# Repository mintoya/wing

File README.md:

# My wireless-ish split keyboard project

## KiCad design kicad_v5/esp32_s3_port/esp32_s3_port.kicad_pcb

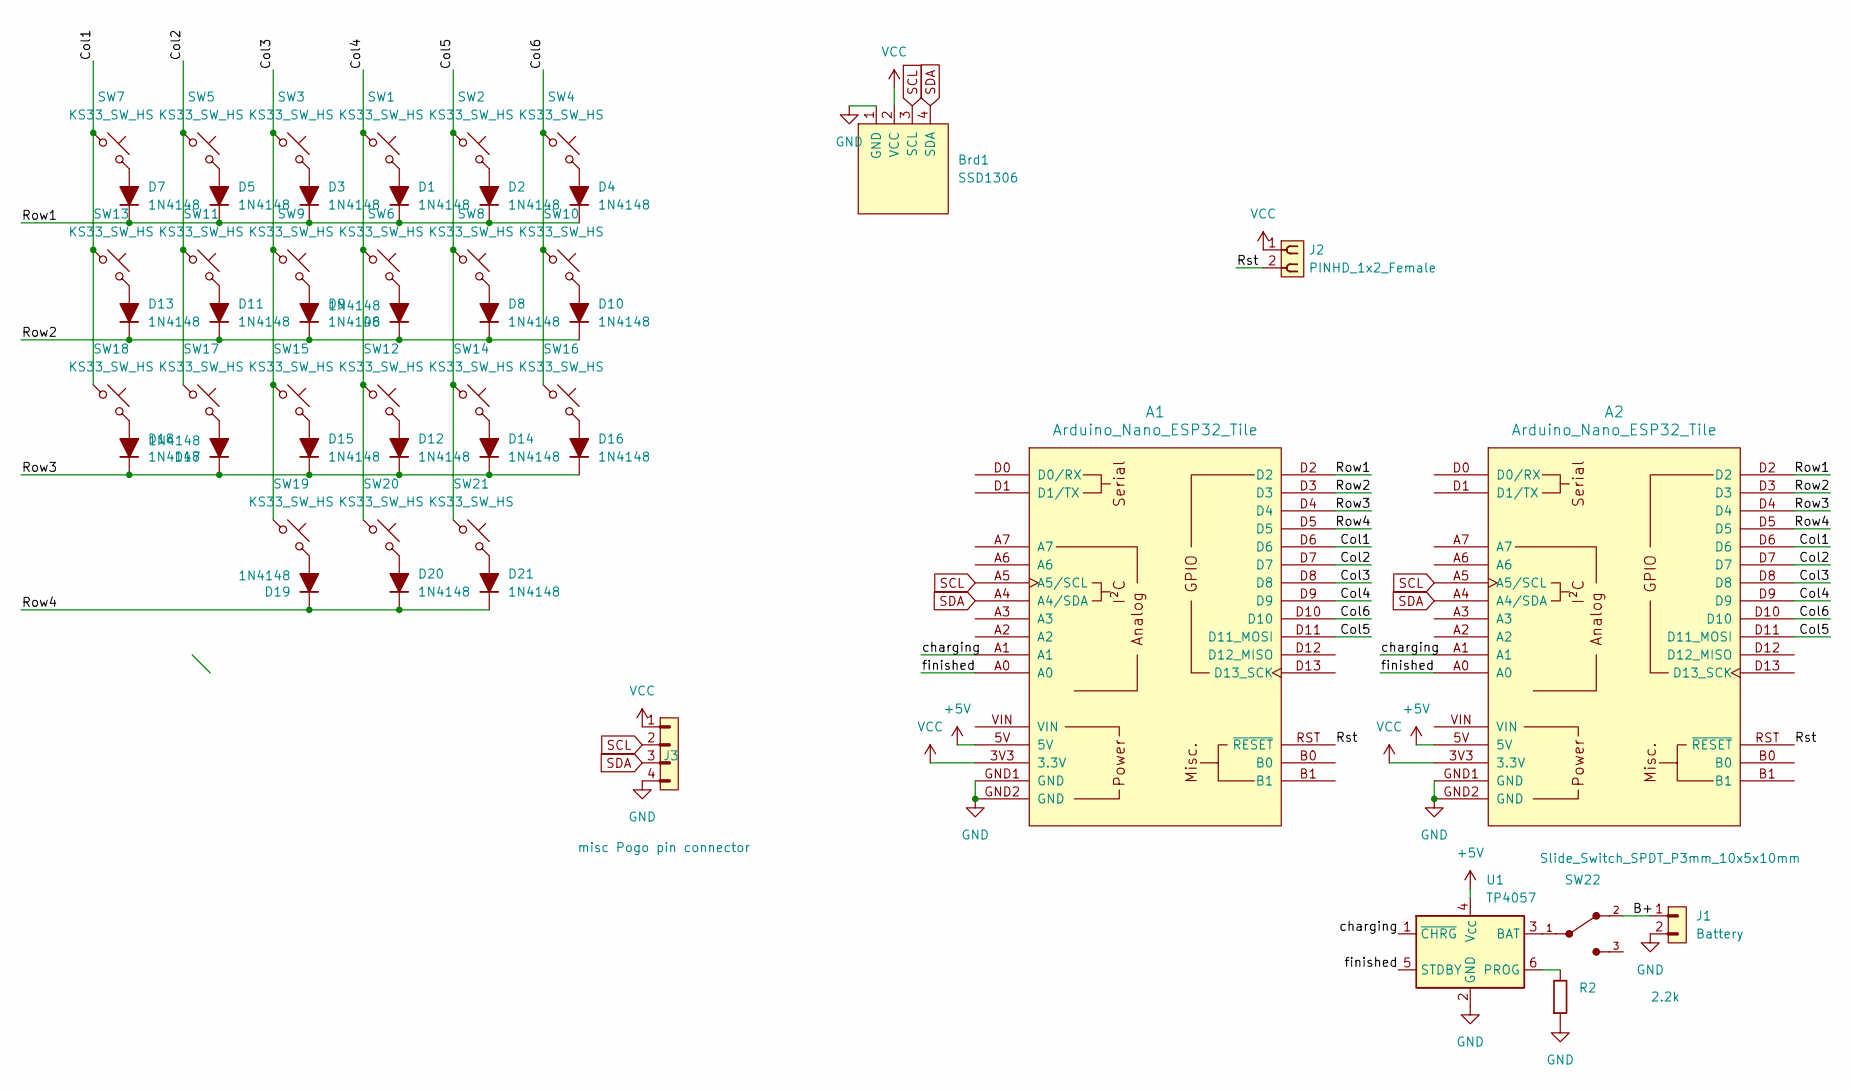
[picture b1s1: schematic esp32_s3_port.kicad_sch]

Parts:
A1, A2: Arduino_Nano_ESP32_Tile
Brd1: SSD1306; 128x64OLED
D1, D2, D3, D4, D5, D6, D7, D8, D9, D10, D11, D12, D13, D14, D15, D16, D17, D18, D19, D20, D21: 1N4148; D_DO-35_SOD27_P7.62mm_Horizontal
J1: Battery; PinHeader_1x02_P2.54mm_Vertical
J2: PINHD_1x2_Female; PinSocket_1x02_P2.54mm_Vertical
J3: misc Pogo pin connector; PinHeader_1x04_P2.54mm_Vertical
R2: 2.2k; R_Axial_DIN0207_L6.3mm_D2.5mm_P10.16mm_Horizontal
SW1, SW2, SW3, SW4, SW5, SW6, SW7, SW8, SW9, SW10, SW11, SW12, SW13, SW14, SW15, SW16, SW17, SW18, SW19, SW20, SW21: KS33_SW_HS; Kailh_socket_PG1350_reversible
SW22: Slide_Switch_SPDT_P3mm_10x5x10mm
U1: TP4057; TSOT-23-6

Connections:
+5V: A1.5V, A2.5V, U1.4 (V_{CC})
/B+: J1.1, SW22.2
/Col1: A1.D6, A2.D6, SW7.1, SW13.1, SW18.1
/Col2: A1.D7, A2.D7, SW5.1, SW11.1, SW17.1
/Col3: A1.D8, A2.D8, SW3.1, SW9.1, SW15.1, SW19.1
/Col4: A1.D9, A2.D9, SW1.1, SW6.1, SW12.1, SW20.1
/Col5: A1.D11 (D11_MOSI), A2.D11 (D11_MOSI), SW2.1, SW8.1, SW14.1, SW21.1
/Col6: A1.D10, A2.D10, SW4.1, SW10.1, SW16.1
/Row1: A1.D2, A2.D2, D1.1 (K), D2.1 (K), D3.1 (K), D4.1 (K), D5.1 (K), D7.1 (K)
/Row2: A1.D3, A2.D3, D6.1 (K), D8.1 (K), D9.1 (K), D10.1 (K), D11.1 (K), D13.1 (K)
/Row3: A1.D4, A2.D4, D12.1 (K), D14.1 (K), D15.1 (K), D16.1 (K), D17.1 (K), D18.1 (K)
/Row4: A1.D5, A2.D5, D19.1 (K), D20.1 (K), D21.1 (K)
/Rst: A1.RST (~RESET), A2.RST (~RESET), J2.2
/charging: A1.A1, A2.A1, U1.1 (~CHRG)
/finished: A1.A0, A2.A0, U1.5 (STDBY)
GND: A1.GND1 (GND), A1.GND2 (GND), A2.GND1 (GND), A2.GND2 (GND), Brd1.1 (GND), J1.2, J3.4, R2.1, U1.2 (GND)
unnamed: D1.2 (A), SW1.2
unnamed: D2.2 (A), SW2.2
unnamed: D3.2 (A), SW3.2
unnamed: D4.2 (A), SW4.2
unnamed: D5.2 (A), SW5.2
unnamed: D6.2 (A), SW6.2
unnamed: D7.2 (A), SW7.2
unnamed: D8.2 (A), SW8.2
unnamed: D9.2 (A), SW9.2
unnamed: D10.2 (A), SW10.2
unnamed: D11.2 (A), SW11.2
unnamed: D12.2 (A), SW12.2
unnamed: D13.2 (A), SW13.2
unnamed: D14.2 (A), SW14.2
unnamed: D15.2 (A), SW15.2
unnamed: D16.2 (A), SW16.2
unnamed: D17.2 (A), SW17.2
unnamed: D18.2 (A), SW18.2
unnamed: D19.2 (A), SW19.2
unnamed: D20.2 (A), SW20.2
unnamed: D21.2 (A), SW21.2
unnamed: SW22.1, U1.3 (BAT)
unnamed: R2.2, U1.6 (PROG)
SCL: A1.A5 (A5/SCL), A2.A5 (A5/SCL), Brd1.3 (SCL), J3.2
SDA: A1.A4 (A4/SDA), A2.A4 (A4/SDA), Brd1.4 (SDA), J3.3
VCC: A1.3V3 (3.3V), A2.3V3 (3.3V), Brd1.2 (VCC), J2.1, J3.1

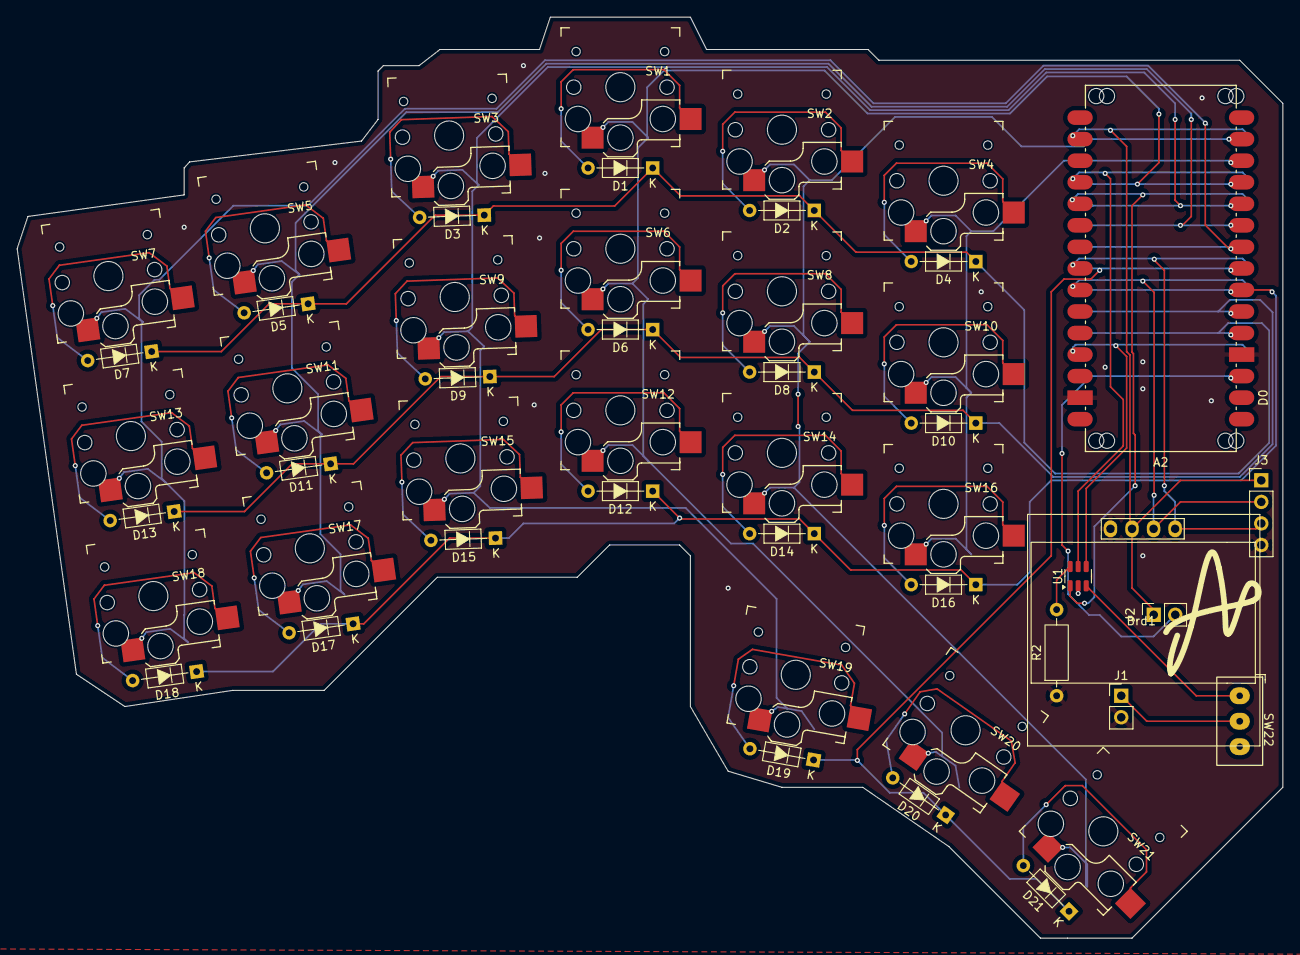
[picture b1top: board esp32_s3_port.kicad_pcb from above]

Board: 2 copper layers, 149.2 x 108.6 mm, 51 parts (1 on the bottom side), 42 nets.

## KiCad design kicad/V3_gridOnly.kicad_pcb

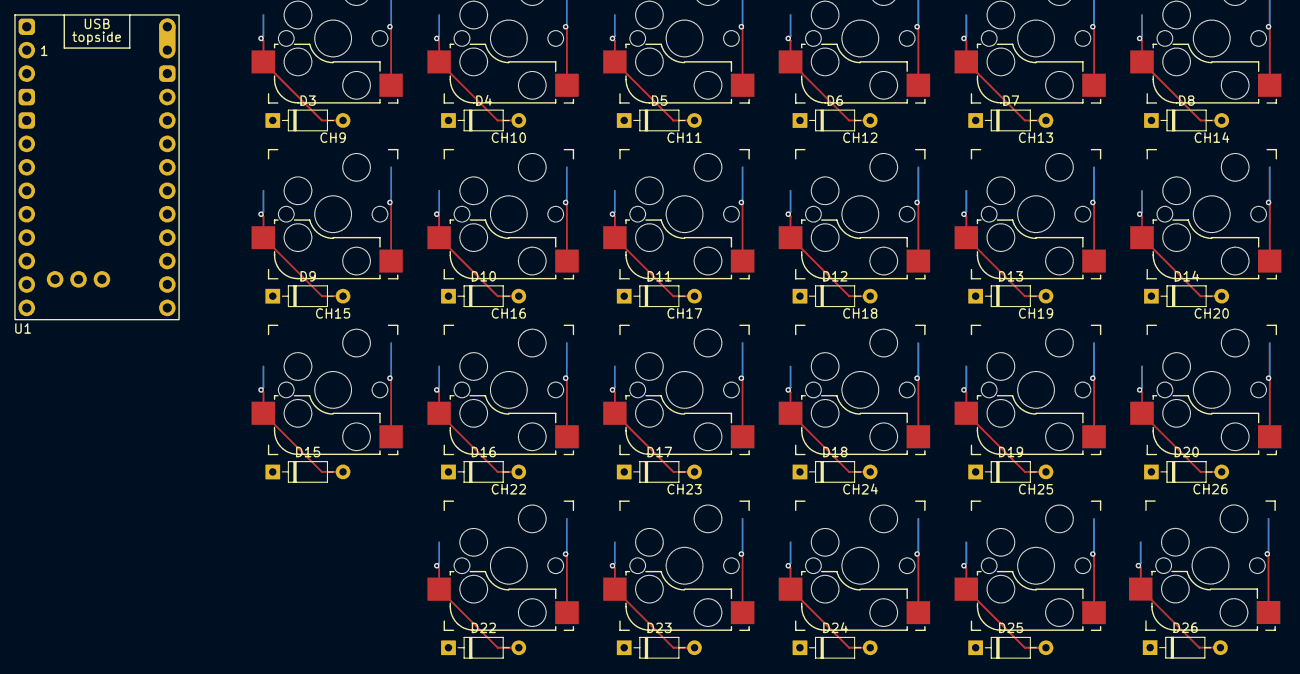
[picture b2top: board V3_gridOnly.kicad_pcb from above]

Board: 2 copper layers, 47 parts (0 on the bottom side), 34 nets.

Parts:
CH3, CH4, CH5, CH6, CH7, CH8, CH9, CH10, CH11, CH12, CH13, CH14, CH15, CH16, CH17, CH18, CH19, CH20, CH22, CH23, CH24, CH25, CH26: KS33_SW_HS; Kailh_socket_MX_reversible
D3, D4, D5, D6, D7, D8, D9, D10, D11, D12, D13, D14, D15, D16, D17, D18, D19, D20, D22, D23, D24, D25, D26: 1N4148; D_DO-35_SOD27_P7.62mm_Horizontal
U1: SuperMini nRF52840; SuperMini_nRF52840_AH_USBup

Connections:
Col1: D3.1 (K), D9.1 (K), D15.1 (K), U1.5 (P0.17)
Col2: D4.1 (K), D10.1 (K), D16.1 (K), D22.1 (K), U1.6 (P0.20)
Col3: D5.1 (K), D11.1 (K), D17.1 (K), D23.1 (K), U1.7 (P0.22)
Col4: D6.1 (K), D12.1 (K), D18.1 (K), D24.1 (K), U1.8 (P0.24)
Col5: D7.1 (K), D13.1 (K), D19.1 (K), D25.1 (K), U1.9 (P1.00)
Col6: D8.1 (K), D14.1 (K), D20.1 (K), D26.1 (K), U1.10 (P0.11)
unnamed: CH3.2, D3.2 (A)
unnamed: CH4.2, D4.2 (A)
unnamed: CH5.2, D5.2 (A)
unnamed: CH6.2, D6.2 (A)
unnamed: CH7.2, D7.2 (A)
unnamed: CH8.2, D8.2 (A)
unnamed: CH9.2, D9.2 (A)
unnamed: CH10.2, D10.2 (A)
unnamed: CH11.2, D11.2 (A)
unnamed: CH12.2, D12.2 (A)
unnamed: CH13.2, D13.2 (A)
unnamed: CH14.2, D14.2 (A)
unnamed: CH15.2, D15.2 (A)
unnamed: CH16.2, D16.2 (A)
unnamed: CH17.2, D17.2 (A)
unnamed: CH18.2, D18.2 (A)
unnamed: CH19.2, D19.2 (A)
unnamed: CH20.2, D20.2 (A)
unnamed: CH22.2, D22.2 (A)
unnamed: CH23.2, D23.2 (A)
unnamed: CH24.2, D24.2 (A)
unnamed: CH25.2, D25.2 (A)
unnamed: CH26.2, D26.2 (A)
unnamed: U1.13 (BAT+), U1.29 (BAT+)
Row1: CH3.1, CH4.1, CH5.1, CH6.1, CH7.1, CH8.1, U1.11 (P1.04-LF)
Row2: CH9.1, CH10.1, CH11.1, CH12.1, CH13.1, CH14.1, U1.12 (P1.06-LF)
Row3: CH15.1, CH16.1, CH17.1, CH18.1, CH19.1, CH20.1, U1.25 (P1.01-LF)
Row4: CH22.1, CH23.1, CH24.1, CH25.1, CH26.1, U1.26 (P1.02-LF)

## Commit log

2025-05-20 init
    most stuff already done
2025-05-20 gitignore
2025-05-20 push
2025-05-21 rounded version added
2025-05-26 firmware
2025-05-26 deletions
2025-05-26 move readme
2025-05-26 move blekeyboard
    had to be moved since the git repo for blekeyboard is currently broken
2025-05-26 added web editor
2025-05-27 keyboard
2025-05-27 change to esp32
2025-05-27 wire cleanup
2025-05-27 key selection
2025-05-29 Cpp list & modes switched to action
2025-05-29 parsing change
2025-05-29 connection + fix
2025-05-29 problematic diodes
    d2 and d34 cannot be used,d2 is the same pin as the builtin led, which
    is used for serial confirmation rn, and d34 is input only
2025-05-29 sleep stuff
2025-05-30 change from global to sheet labels
2025-05-31 battery chargin module additon
2025-05-31 usp+uart converter
2025-05-31 switch
2025-06-01 removed false connections
    that footprint is wrong
2025-06-01 fixed connections and pin#
2025-06-01 changed uart-hid pinout
2025-06-01 slkscreen
2025-06-01 stuff
2025-06-01 power
    shouldnt be charging and discharging now i think
2025-06-01 positoins
2025-06-01 wiring
2025-06-01 positioning
2025-06-01 filled area
2025-06-02 lots of changes
    usb module support and more fixed wirign
2025-06-02 schmatic changes
    voltage divider now used for batter ypercentage calculation.
    power-OR used as voltage supply
2025-06-02 schematic
2025-06-03 chip change
    changed the module to use the ch9329(chip) instead of the ch9328 (board)
2025-06-03 added signature ig
2025-06-04 switches change
    switches no longer use heirarchical schematic
2025-06-04 outline changes
2025-06-05 graphic change
2025-06-10 power
2025-07-21 nrf version
2025-07-21 routing
2025-07-23 full routing
2025-07-24 routing cleanup
    freerouting moment
2025-07-24 outline svg
2025-07-25 nrf completed
2025-07-26 ignore
2025-08-02 new firmware + new kicad
2025-08-03 source update
    new umap class
2025-08-04 lots of updates
2025-08-04 more changes
2025-08-04 bluetooth worksish
2025-08-04 keycode referance
2025-08-05 hid update
2025-08-06 umap types
2025-08-06 keymap workin
2025-08-06 sync
2025-08-08 example connection
2025-08-12 working version
2025-08-13 errror detection and higher data rate
2025-08-13 even higher baud rate
    a simple wait fixed almost everything
2025-08-14 layers
    added support for key layers
2025-08-15 layers+ function
2025-08-16 tapdance progress
2025-08-17 working tapdances
    working version of tapdances added, timout is a #defined constantt
    length is unused(probably unsafe)
2025-08-17 ergogen file
2025-08-19 direcion keys
2025-09-06 esp32 version
2025-09-06 new ergogen
2025-09-06 move some files
2025-09-06 signature
2025-09-07 parts
2025-09-07 ssd 1306
2025-09-07 battery switch
2025-09-15 ui rewrite
2025-09-16 selection
    key order follows firmware key order
2025-09-21 layers
2025-09-24 hardware update
    lots of items were switced with the equivalent headers
2025-09-25 software upodate
2025-09-26 layout parsing
2025-09-26 web now connected to the rest
2025-09-26 persistant state
2025-09-27 tapdances
2025-09-27 less annoying webpage
2025-09-27 integer converison
2025-09-27 more externs
2025-09-27 my-lib as submodule
2025-09-27 symlinks were broken
2025-09-27 symlinks
    symlinks work in linux
2025-09-27 kml names
2025-09-28 serials
2025-09-28 serial interface change
2025-09-28 styles
2025-09-28 some ui stuff
2025-09-28 surface mount version
2025-09-29 moved valid key values
2025-09-29 return formatting
2025-10-02 web and board actually connected now
2025-10-02 transitions
2025-10-02 tapdance interrupt + name changes
2025-10-03 state machine ffix
2025-10-06 web part upgreade
2025-10-07 web full overhaul
2025-10-07 removing tapdances
2025-10-08 pages init
2025-10-08 pages shenanigans
2025-10-19 remove stls
2025-10-22 filesystem fix
2025-10-22 remove unused
2025-10-22 wire clock
2025-10-23 submodule crc update
    maybe reduce redundancy later
2025-10-23 filesystem
    filesystem wasnt broken, the board was
2025-10-24 submodule update
2026-02-10 update my-lib to wheels
2026-02-13 migrated my lib
2026-02-14 broken version
2026-02-14 new main file
2026-02-14 main update
2026-02-15 shouldnt have had that in there
2026-02-16 command parsing
2026-02-17 half sync
2026-02-17 peripheral update
2026-02-17 move from wire to serial
2026-02-17 minihash
2026-02-18 new comms
2026-02-18 example
2026-02-19 sped up serial
2026-02-19 default layout
2026-02-24 default layout update
2026-02-24 Update my-lib
2026-02-24 constexpr
2026-02-24 changed
2026-02-26 layers fix
2026-03-04 new key
2026-03-04 layout
2026-03-07 move to mylist
2026-03-07 simplified keyboard state machines
2026-03-08 new presskeys
2026-03-10 Add GitHub Actions workflow for building WASM
2026-03-10 Modify WASM build command in workflow
    Updated emcc command to compile C++ with additional flags.
2026-03-10 Change default branch from 'main' to 'master'
2026-03-10 Update build-wasm.yml to use workflow_dispatch
    Change trigger to manual dispatch for WASM build.
2026-03-10 Fix path separator in build-wasm.yml
2026-03-10 Modify WASM build process to use new source path
    Updated the emcc command to compile from a new source path.
2026-03-10 fix submodule
2026-03-10 remove .gitmodule
2026-03-10 remove submodule
2026-03-10 gitmodule
2026-03-10 Update build-wasm workflow submodules
    Changed submodule checkout behavior and added manual submodule initialization step.
2026-03-10 Simplify file copy commands in build-wasm.yml
2026-03-10 Update path for vason.js in build-wasm workflow
2026-03-10 Fix path for vason.js in build-wasm workflow
2026-03-10 Auto-compile WASM and update docs
2026-03-10 update to vason
2026-03-10 Update artifact upload path in static.yml
    Change artifact upload path to './docs' for GitHub Pages deployment.
2026-03-10 modulefactory
2026-03-10 wasm change
2026-03-10 idk?
2026-03-10 change path
2026-03-10 workflow
2026-03-11 vason
2026-03-11 kinda working version
2026-03-11 just vason_arrr
2026-03-11 move stem
2026-03-11 cursed
2026-03-12 tapdances fix
2026-03-12 web fix
